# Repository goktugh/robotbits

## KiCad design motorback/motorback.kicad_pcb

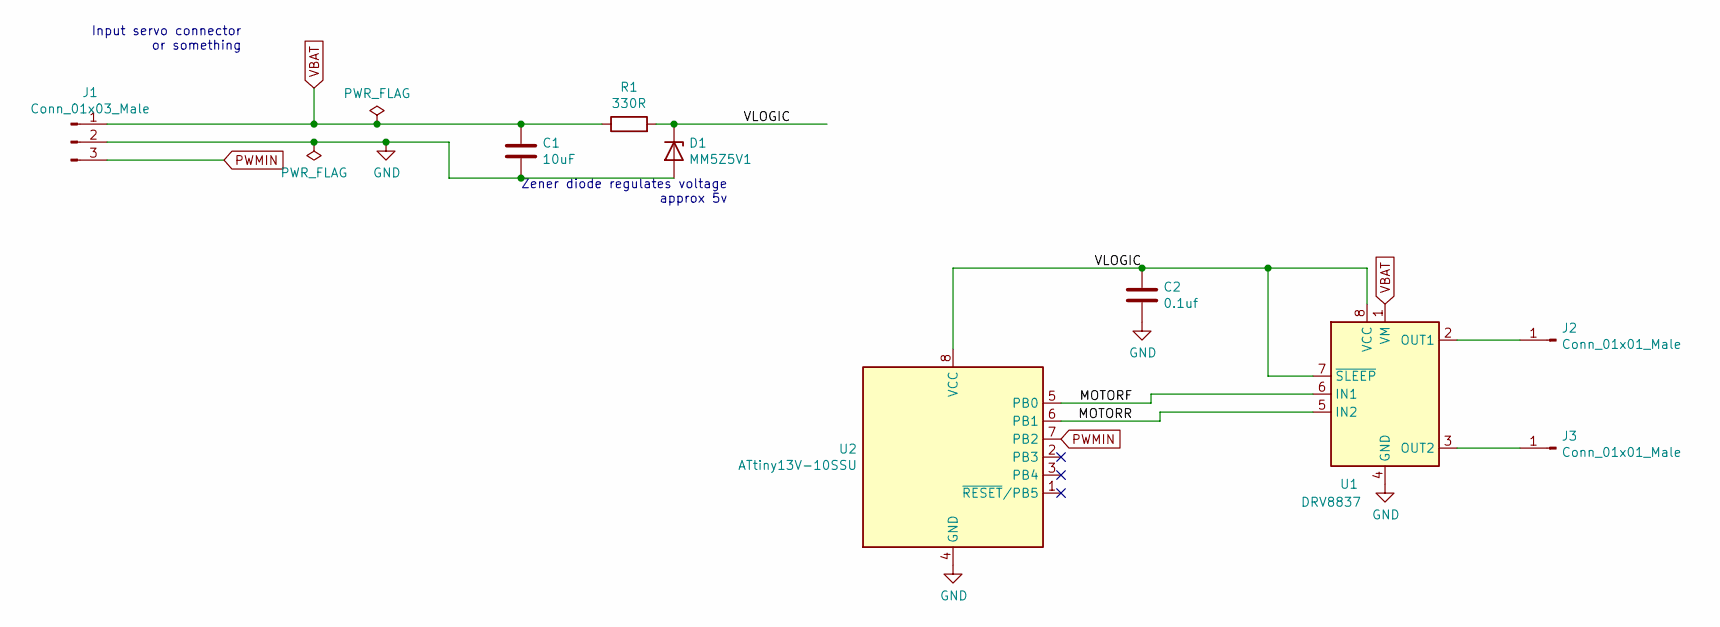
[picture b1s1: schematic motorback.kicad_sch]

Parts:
C1: 10uF; C_0603_1608Metric
C2: 0.1uf; C_0603_1608Metric
D1: MM5Z5V1; D_SOD-523; LCSC C55848
J1: Conn_01x03_Male; JST_SH_SM03B-SRSS-TB_1x03-1MP_P1.00mm_Horizontal
J2, J3: Conn_01x01_Male; motorpad
R1: 330R; R_0603_1608Metric
U1: DRV8837; drv8837_custom
U2: ATtiny13V-10SSU; SOIC-8_3.9x4.9mm_P1.27mm

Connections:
/CONFIG1: U2.2 (PB3); also elsewhere on the board
/MOTORF: U1.6 (IN1), U2.5 (PB0)
/MOTORR: U1.5 (IN2), U2.6 (PB1)
/VLOGIC: C2.1, D1.1 (K), R1.2, U1.7 (~SLEEP), U1.8 (VCC), U2.8 (VCC)
GND: C1.2, C2.2, D1.2 (A), J1.2, U1.4 (GND), U1.9 (GND), U2.4 (GND); also elsewhere on the board
unnamed: J2.1, U1.2 (OUT1)
unnamed: J3.1, U1.3 (OUT2)
PWMIN: J1.3, U2.7 (PB2)
VBAT: C1.1, J1.1, R1.1, U1.1 (VM)

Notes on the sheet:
Input servo connector or something
Zener diode regulates voltage approx 5v

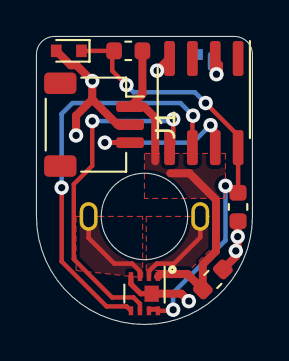
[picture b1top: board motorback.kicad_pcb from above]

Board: 2 copper layers, 12.0 x 16.0 mm, 10 parts (1 on the bottom side), 9 nets.

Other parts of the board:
JP1: Jumper; SolderJumper-2_P1.3mm_Bridged_Pad1.0x1.5mm

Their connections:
/CONFIG1: JP1.2; also elsewhere on the board
GND: JP1.1; also elsewhere on the board
